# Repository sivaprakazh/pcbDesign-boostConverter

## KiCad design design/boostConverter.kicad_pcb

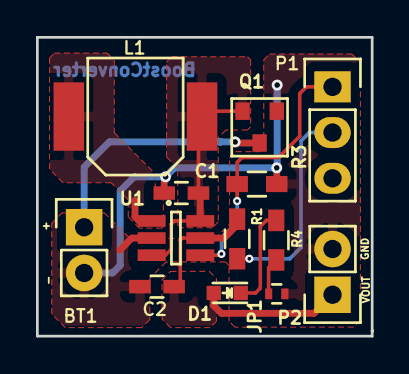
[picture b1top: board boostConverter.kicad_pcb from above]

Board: 2 copper layers, 18.6 x 16.6 mm, 14 parts (1 on the bottom side), 9 nets.

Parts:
BT1: AA; Pin_Header_Straight_1x02
C1: 4.7uF; C_0603_HandSoldering
C2: 10uF; C_0603_HandSoldering
D1: LED; LED_0603
JP1: JPR; R_0402
L1: 4.7uH; Inductor ELL-6S
P1: CN1X3; Pin_Header_Straight_1x03
P2: CN1X2; Pin_Header_Straight_1x02
Q1: MFET; P_MOSFET
R1: 536K; R_0603_HandSoldering
R2: 442K; R_0603_HandSoldering
R3: 309K; R_0603_HandSoldering
R4: 7.1K; R_0603_HandSoldering
U1: MCP1460; SOT-23-6_Handsoldering

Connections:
GND: BT1.2, C1.2, C2.2, JP1.2, P2.2, Q1.1, R3.2, U1.2
unnamed: BT1.1, Q1.3
unnamed: C1.1, L1.1, Q1.2, U1.3, U1.6
unnamed: C2.1, D1.2, P2.1, R1.1, U1.5
unnamed: D1.1, R4.1
unnamed: JP1.1, R4.2
unnamed: L1.2, U1.1
unnamed: P1.1, R2.2, R3.1, U1.4
unnamed: P1.2, R1.2, R2.1

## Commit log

2016-10-01 newproject
